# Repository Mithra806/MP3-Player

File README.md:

# MP3 Player — KiCad Hardware Project

A rechargeable MP3 player I designed from scratch in KiCad. It's got buttons
for playback control and a small screen that shows what track is playing.

## What it does
- Charges over USB
- Plays MP3s off a microSD card, using a DFPlayer Mini module
- Headphone output via a 3.5mm jack
- Two buttons for next/previous track and volume
- An OLED screen shows the current track, driven by an Arduino Nano reading
  data from the DFPlayer Mini (not programmed yet)
- A power switch to turn the whole thing on/off

## Bill of Materials
| Ref | Component | Value/Notes | Qty | Link |
|-----|-----------|-------------|-----|------|
| BT1 | 18650 Li-ion Battery | 3.7V rechargeable cell | 1 | [Link](#) |
| SW1 | Slide/Toggle Switch | Power switch, SPST | 1 | [Link](#) |
| SW2 | Pushbutton | Next track (wired to DFPlayer IO1) | 1 | [Link](#) |
| SW3 | Pushbutton | Previous track (wired to DFPlayer IO2) | 1 | [Link](#) |
| SW4 | Pushbutton | Pause/Unpause (wired to Arduino D2) | 1 | [Link](#) |
| U1 | TP4056-42-ESOP8 | Li-ion charger IC | 1 | [Link](#) |
| U2 | DFPlayer Mini | MP3 playback module | 1 | [Link](#) |
| U3 | OLED Display | ER-OLEDM0.91-1x-I2C (SSD1306-based) | 1 | [Link](#) |
| A1 | Arduino Nano v3.x | Microcontroller | 1 | [Link](#) |
| J1 | 3.5mm Audio Jack | Mono, 5-pin | 1 | [Link](#) |
| J2 | USB Micro-B Connector | Charging input | 1 | [Link](#) |
| R1 | Resistor | 2kΩ (sets TP4056 charge current) | 1 | [Link](#) |
| — | microSD Card | Stores audio files for DFPlayer | 1 | [Link](#) |
| — | Headphones/Speaker | Audio output | 1 | [Link](#) |

## Schematic

## PCB Layout

## 3D Render

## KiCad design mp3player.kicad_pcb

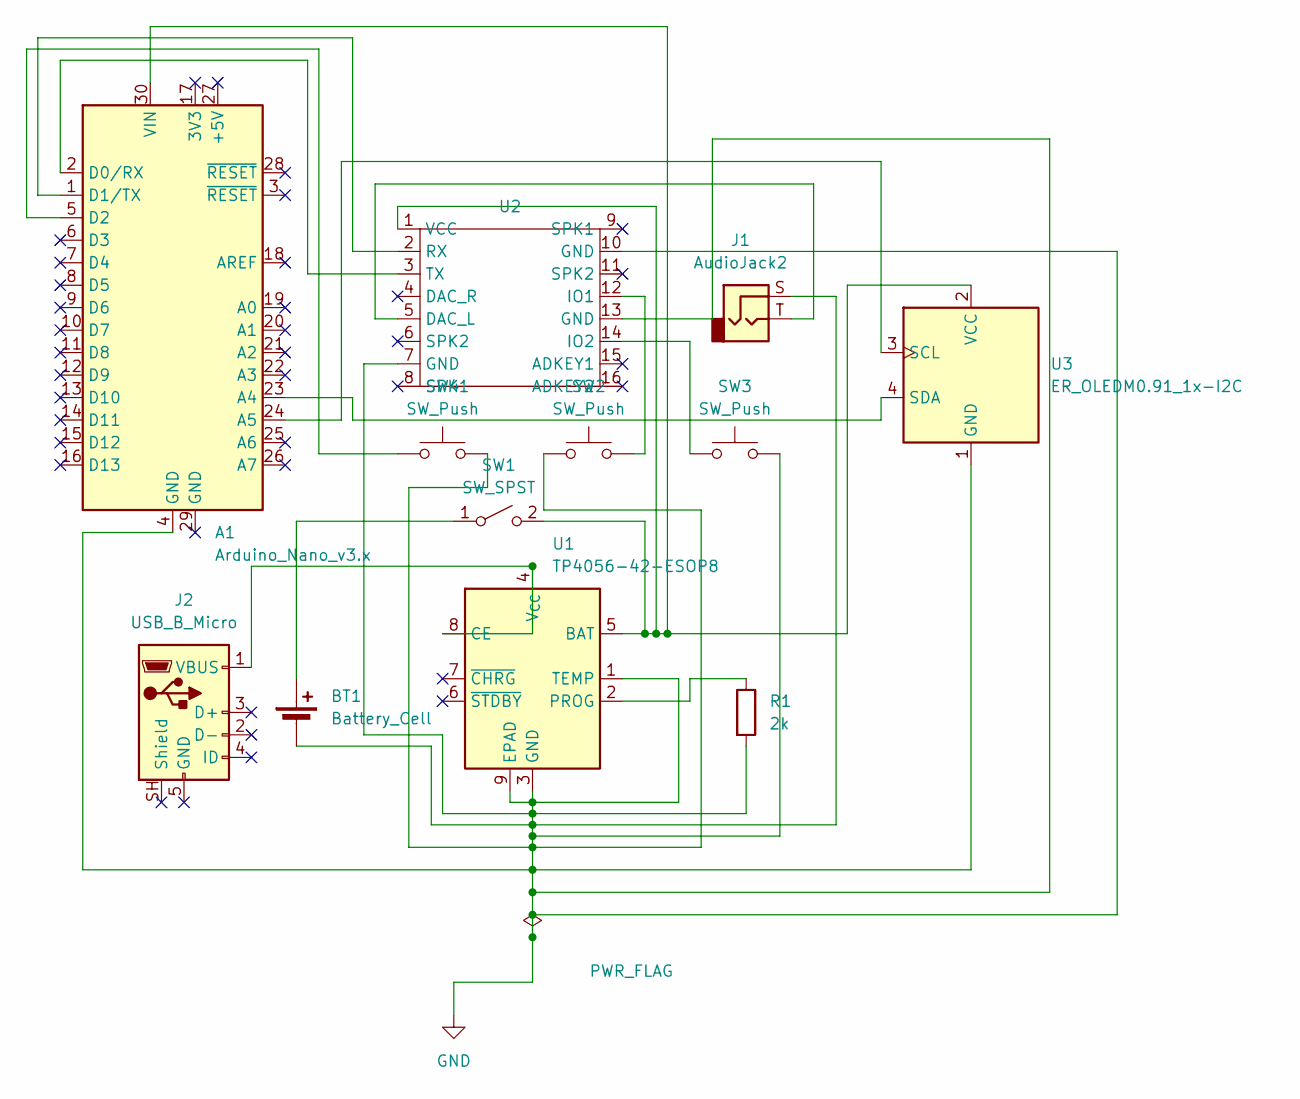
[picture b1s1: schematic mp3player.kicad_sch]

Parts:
A1: Arduino_Nano_v3.x; Arduino_Nano
BT1: Battery_Cell; BatteryHolder_Keystone_1042_1x18650
J1: AudioJack2; Jack_3.5mm_CUI_SJ1-3535NG_Horizontal
J2: USB_B_Micro; USB_Micro-B_Molex-105017-0001
R1: 2k; R_Axial_DIN0207_L6.3mm_D2.5mm_P10.16mm_Horizontal
SW1: SW_SPST; SW_SPST_Omron_B3F-40xx
SW2, SW3, SW4: SW_Push; SW_PUSH_6mm_H5mm
U1: TP4056-42-ESOP8; SOIC-8-1EP_3.9x4.9mm_P1.27mm_EP2.41x3.3mm_ThermalVias
U2: DFPlayer_Mini
U3: ER_OLEDM0.91_1x-I2C

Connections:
GND: A1.4 (GND), BT1.2 (-), J1.S, R1.2, SW2.1, SW3.2, SW4.2, U1.1 (TEMP), U1.3 (GND), U1.9 (EPAD), U2.7 (GND), U2.10 (GND), U2.13 (GND), U3.1 (GND)
unnamed: A1.23 (A4), U3.4 (SDA)
unnamed: A1.24 (A5), U3.3 (SCL)
unnamed: A1.2 (D0/RX), U2.3 (TX)
unnamed: A1.1 (D1/TX), U2.2 (RX)
unnamed: A1.5 (D2), SW4.1
unnamed: A1.30 (VIN), SW1.2 (B), U1.5 (BAT), U2.1 (VCC), U3.2 (VCC)
unnamed: BT1.1 (+), SW1.1 (A)
unnamed: J2.1 (VBUS_1), U1.4 (V_{CC}), U1.8 (CE)
unnamed: R1.1, U1.2 (PROG)
unnamed: J1.T, U2.5 (DAC_L)
unnamed: SW2.2, U2.12 (IO1)
unnamed: SW3.1, U2.14 (IO2)

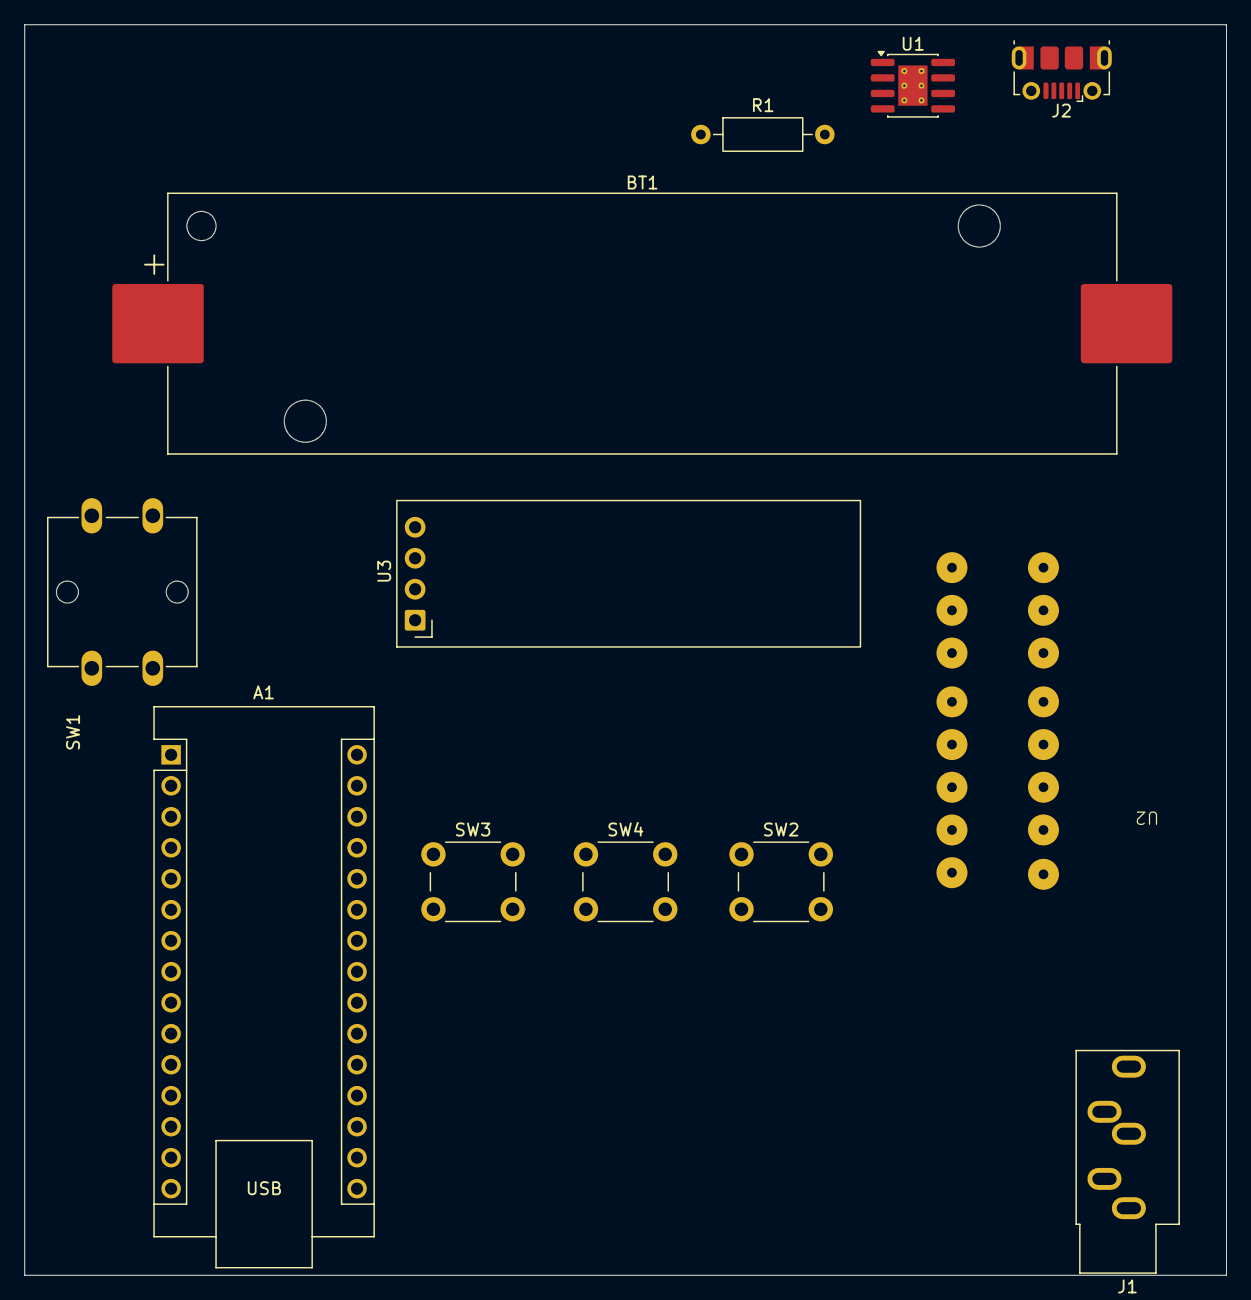
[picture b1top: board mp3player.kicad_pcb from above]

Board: 2 copper layers, 98.5 x 102.5 mm, 12 parts (0 on the bottom side), 13 nets.
